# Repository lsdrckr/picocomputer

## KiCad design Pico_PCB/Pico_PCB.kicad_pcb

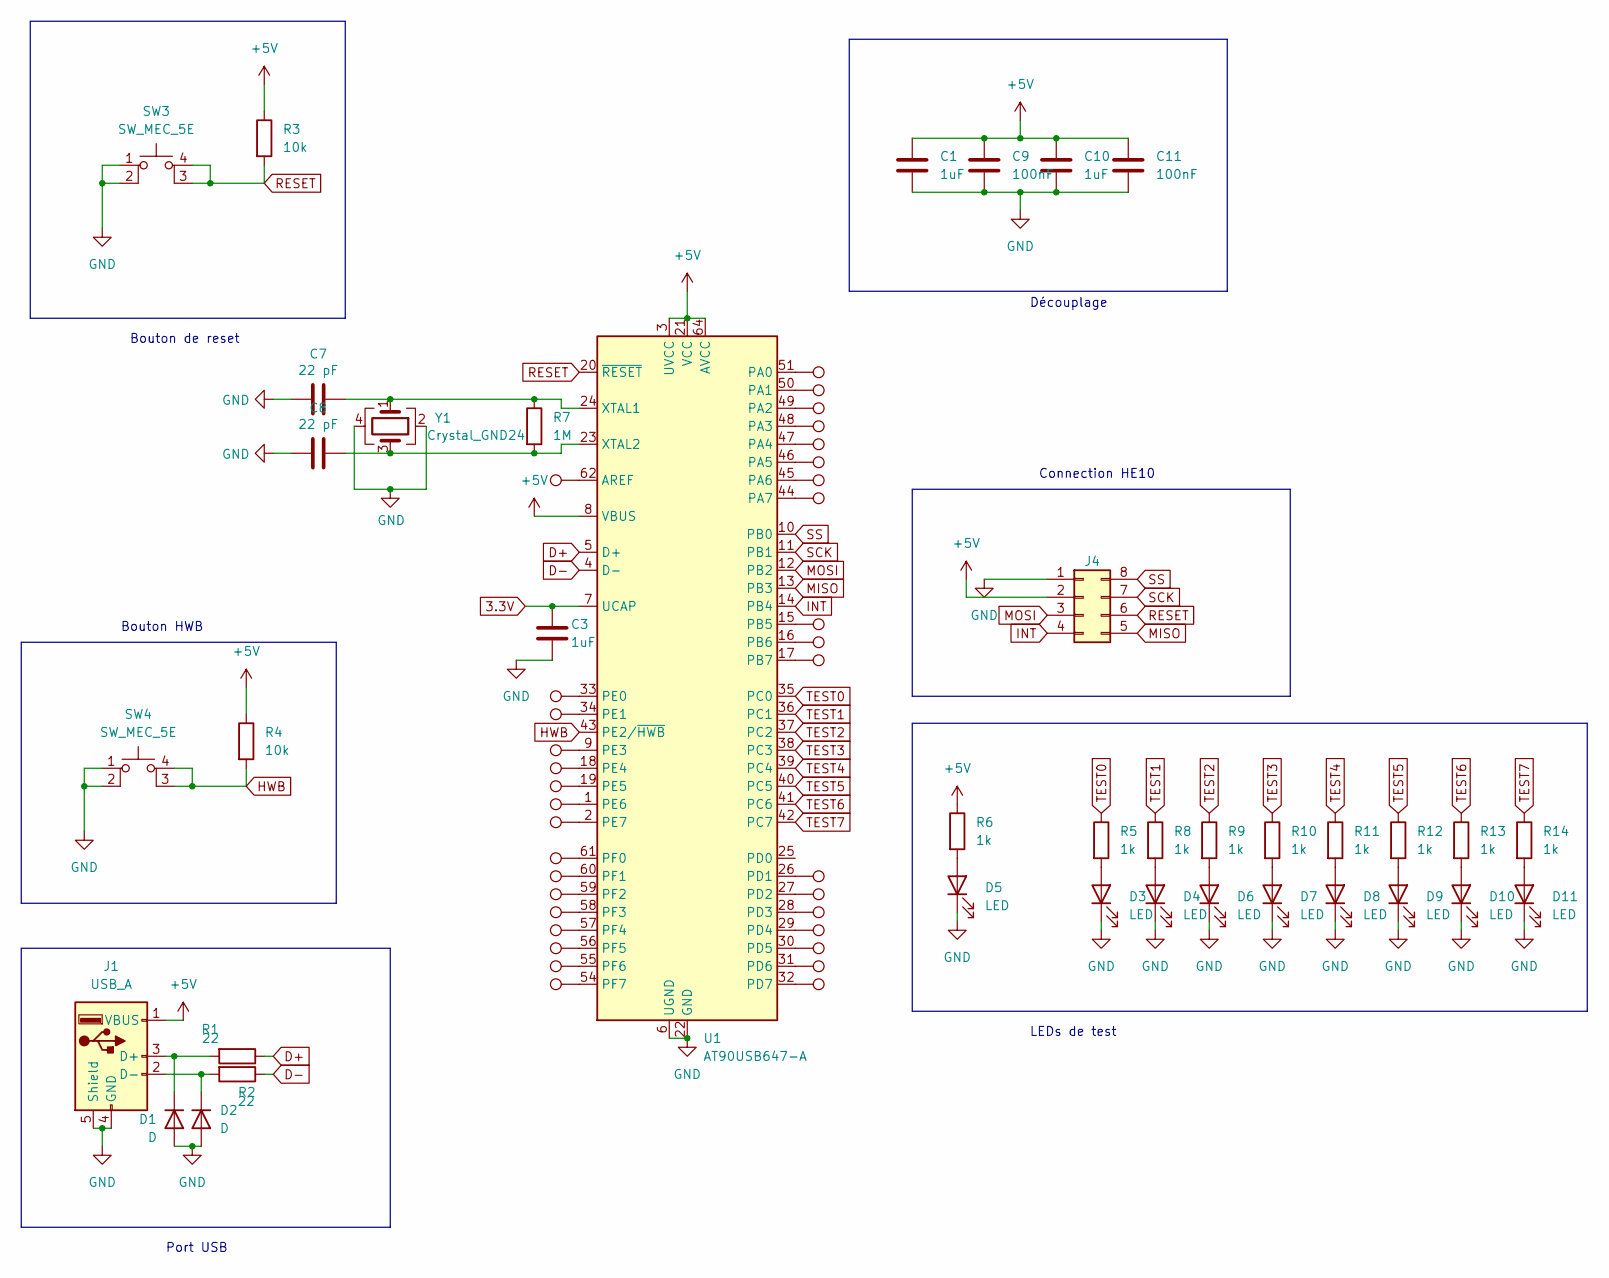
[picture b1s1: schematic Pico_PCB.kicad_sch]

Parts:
C1, C3, C10: 1uF; C_0603_1608Metric_Pad1.08x0.95mm_HandSolder
C7, C8: 22 pF; C_0603_1608Metric_Pad1.08x0.95mm_HandSolder
C9, C11: 100nF; C_0603_1608Metric_Pad1.08x0.95mm_HandSolder
D1, D2: D; D_0603_1608Metric_Pad1.05x0.95mm_HandSolder
D3, D4, D5, D6, D7, D8, D9, D10, D11: LED; LED_0603_1608Metric_Pad1.05x0.95mm_HandSolder
J1: USB_A; USB-A-S-NOSILK-FEMALE
J4: Conn_02x04_Counter_Clockwise; IDC-Header_2x04_P2.54mm_Vertical
R1, R2: 22; R_0603_1608Metric_Pad0.98x0.95mm_HandSolder
R3, R4: 10k; R_0603_1608Metric_Pad0.98x0.95mm_HandSolder
R5, R6, R8, R9, R10, R11, R12, R13, R14: 1k; R_0603_1608Metric_Pad0.98x0.95mm_HandSolder
R7: 1M; R_0603_1608Metric_Pad0.98x0.95mm_HandSolder
SW3, SW4: SW_MEC_5E; TACTILE_SWITCH_SMD_5.2MM
TP1, TP2, TP3, TP4, TP5, TP6, TP7, TP8, TP9, TP10, TP11, TP13, TP14, TP15, TP16, TP17, TP18, TP19, TP20, TP21, TP22, TP23, TP24, TP25, TP26, TP27, TP28, TP29, TP30, TP31, TP32, TP33, TP34, TP35: TestPoint; TestPoint_THTPad_D1.5mm_Drill0.7mm
U1: AT90USB647-A; TQFP-64_14x14mm_P0.8mm
Y1: Crystal_GND24; Crystal_SMD_SeikoEpson_FA238-4Pin_3.2x2.5mm_HandSoldering

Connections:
3.3V: C3.1, U1.7 (UCAP)
+5V: C1.1, C9.1, C10.1, C11.1, J1.1 (VBUS), J4.2, R3.1, R4.1, R6.1, U1.3 (UVCC), U1.8 (VBUS), U1.21 (VCC), U1.52 (VCC), U1.64 (AVCC)
D+: R2.1, U1.5 (D+)
D-: R1.1, U1.4 (D-)
GND: C1.2, C3.2, C7.2, C8.2, C9.2, C10.2, C11.2, D1.2 (A), D2.2 (A), D3.1 (K), D4.1 (K), D5.1 (K), D6.1 (K), D7.1 (K), D8.1 (K), D9.1 (K), D10.1 (K), D11.1 (K), J1.4 (GND), J1.5 (Shield), J4.1, SW3.1, SW3.2, SW4.1, SW4.2, U1.6 (UGND), U1.22 (GND), U1.53 (GND), U1.63 (GND), Y1.2, Y1.4
HWB: R4.2, SW4.3 (K), SW4.4 (A), U1.43 (PE2/~HWB)
INT: J4.4, U1.14 (PB4)
MISO: J4.5, U1.13 (PB3)
MOSI: J4.3, U1.12 (PB2)
unnamed: D1.1 (K), J1.3 (D+), R2.2
unnamed: D2.1 (K), J1.2 (D-), R1.2
unnamed: D3.2 (A), R5.2
unnamed: D4.2 (A), R8.2
unnamed: D5.2 (A), R6.2
unnamed: D6.2 (A), R9.2
unnamed: D7.2 (A), R10.2
unnamed: D8.2 (A), R11.2
unnamed: D9.2 (A), R12.2
unnamed: D10.2 (A), R13.2
unnamed: D11.2 (A), R14.2
unnamed: TP22.1, U1.62 (AREF)
unnamed: TP1.1, U1.51 (PA0)
unnamed: TP2.1, U1.50 (PA1)
unnamed: TP3.1, U1.49 (PA2)
unnamed: TP4.1, U1.48 (PA3)
unnamed: TP5.1, U1.47 (PA4)
unnamed: TP6.1, U1.46 (PA5)
unnamed: TP7.1, U1.45 (PA6)
unnamed: TP8.1, U1.44 (PA7)
unnamed: TP9.1, U1.15 (PB5)
unnamed: TP10.1, U1.16 (PB6)
unnamed: TP11.1, U1.17 (PB7)
unnamed: TP13.1, U1.26 (PD1)
unnamed: TP14.1, U1.27 (PD2)
unnamed: TP15.1, U1.28 (PD3)
unnamed: TP16.1, U1.29 (PD4)
unnamed: TP17.1, U1.30 (PD5)
unnamed: TP18.1, U1.31 (PD6)
unnamed: TP19.1, U1.32 (PD7)
unnamed: TP23.1, U1.33 (PE0)
unnamed: TP35.1, U1.34 (PE1)
unnamed: TP24.1, U1.9 (PE3)
unnamed: TP25.1, U1.18 (PE4)
unnamed: TP26.1, U1.19 (PE5)
unnamed: TP27.1, U1.1 (PE6)
unnamed: TP28.1, U1.2 (PE7)
unnamed: TP29.1, U1.61 (PF0)
unnamed: TP30.1, U1.60 (PF1)
unnamed: TP31.1, U1.59 (PF2)
unnamed: TP32.1, U1.58 (PF3)
unnamed: TP33.1, U1.57 (PF4)
unnamed: TP34.1, U1.56 (PF5)
unnamed: TP21.1, U1.55 (PF6)
unnamed: TP20.1, U1.54 (PF7)
unnamed: C7.1, R7.1, U1.24 (XTAL1), Y1.1
unnamed: C8.1, R7.2, U1.23 (XTAL2), Y1.3
RESET: J4.6, R3.2, SW3.3 (K), SW3.4 (A), U1.20 (~RESET)
SCK: J4.7, U1.11 (PB1)
SS: J4.8, U1.10 (PB0)
TEST0: R5.1, U1.35 (PC0)
TEST1: R8.1, U1.36 (PC1)
TEST2: R9.1, U1.37 (PC2)
TEST3: R10.1, U1.38 (PC3)
TEST4: R11.1, U1.39 (PC4)
TEST5: R12.1, U1.40 (PC5)
TEST6: R13.1, U1.41 (PC6)
TEST7: R14.1, U1.42 (PC7)

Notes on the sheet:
LEDs de test
Bouton de reset
Découplage
Bouton HWB
Port USB
Connection HE10

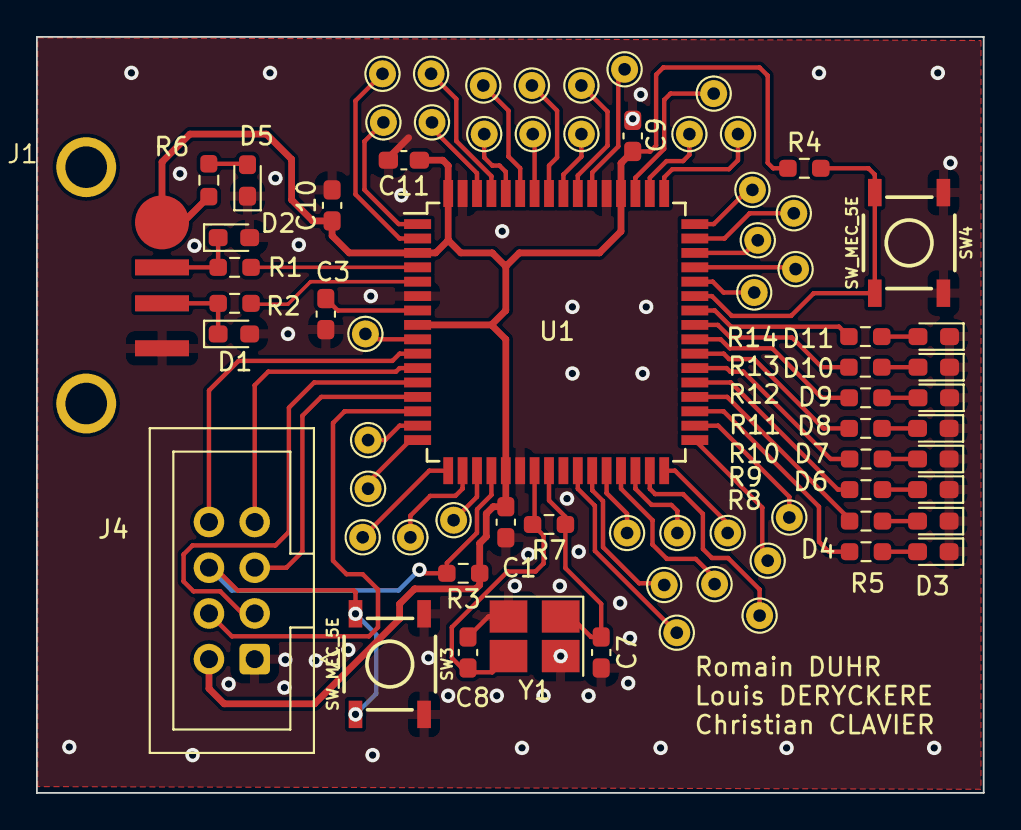
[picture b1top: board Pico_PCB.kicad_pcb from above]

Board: 2 copper layers, 52.6 x 42.0 mm, 72 parts (0 on the bottom side), 67 nets.

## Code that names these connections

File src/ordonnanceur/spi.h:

#ifndef __SPI_H__
#define __SPI_H__

#include <avr/io.h>
#include <util/delay.h>
#include <avr/interrupt.h>

#define CTC1    WGM12
#define MISO    PB4
#define MOSI    PB3
#define SCK     PB5
#define SS      PB2
#define SS2     PC0
#define SS3     PC3
#define SS4     PD1
#define SS5     PD4
#define SS6     PD7
#define RST1    PC1
#define NB_TASK 5
#define SLEEP   0
#define AWAKE   1

void initSPI();
void selectSlaveSPI(volatile uint8_t *ssPort, volatile uint8_t ss){;
void unselectSlaveSPI(volatile uint8_t *ssPort, volatile uint8_t ss);
uint8_t transferSPI(uint8_t data);
int main();

#endif

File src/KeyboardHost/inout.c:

#include "inout.h"

volatile uint8_t leds[NB_LED] = {PC7, PC6, PC5, PC4, PC3, PC2, PC1, PC0};
buffer_t buffer;
int sizeSendFlag = 0;

void initSPISlave() {
    // Configurer le port MISO comme sortie 
    DDRB |= (1<<MISO);
    // Configurer le port MOSI SCK SS comme entrée
    DDRB &= ~(1 <<MOSI);
    DDRB &= ~(1<<SCK);
    DDRB &= ~(1<<SS);

    // Actvier le mode SPI
    SPCR |= (1<<SPE);

    // Actver mode esclave SPI
    SPCR &= ~(1 << MSTR);

    // Activer l'interruption SPI
    SPCR |= (1 << SPIE);

    // Activer les interruptions globales
    sei();
}

void initIO(){
    // Initialisation des leds
    for(int i=0; i<NB_LED; i++){
        DDRC |= (1<<leds[i]);
    }

    // Initialisation du buffer 
    buffer.head = -1;
    buffer.tail = -1;
    
    // Interruption slave->master
    DDRB |= (1<<INT);
    setLowOutput(&PORTB, INT);

    // Init flag d'envoi de la taille
    sizeSendFlag = 0;

    // Init spi
    initSPISlave();
    sei();
}

uint8_t isEmpty(){
    return buffer.head == -1;
}

uint8_t isFull() {
    return (buffer.tail + 1) % MAX_DATA == buffer.head;
}

uint8_t sizeBuffer(){
    if(isEmpty()) return 0;
    if(buffer.tail < buffer.head)
        return MAX_DATA - (buffer.head - buffer.tail) + 1;
    return buffer.tail - buffer.head + 1;
}

void enqueue(char key){
    if (isFull()) {
        return;
    }
    
    buffer.tail = (buffer.tail + 1) % MAX_DATA;

    buffer.data[buffer.tail] = key;
    if (isEmpty()) {
        buffer.head = 0;
    }
}

char dequeue(){
    if (isEmpty()) {
        return 0x00;
    }
    char key = buffer.data[buffer.head];

    if (buffer.head == buffer.tail) {
        // Le buffer est maintenant vide
        buffer.head = -1;
        buffer.tail = -1;
    } else {
        buffer.head = (buffer.head + 1) % MAX_DATA;
    }
    return key;
}

void setHighOutput(volatile uint8_t *port, volatile uint8_t pin){
    *port |= (1<<pin);
}

void setLowOutput(volatile uint8_t *port, volatile uint8_t pin){
	*port &= ~(1<<pin);
}

void reverseOutput(volatile uint8_t *port, volatile uint8_t pin){
    *port ^= (1<<pin);
}

void printLeds(char c){
    for(int i=0; i<NB_LED; i++){
        if(((c >> i) & 1) == 1){
            setHighOutput(&PORTC, leds[i]);
        }else{
            setLowOutput(&PORTC, leds[i]);
        }
    }
}

void clearLeds(){
    for(int i=0; i<NB_LED; i++){
        setLowOutput(&PORTC, leds[i]);
    }
}

void keyHandler(char key){
    // Sauvegarde de la clef
    enqueue(key);
    // Envoie de l'interruption
    setHighOutput(&PORTB, INT); 
}

ISR(SPI_STC_vect) {
    uint8_t receivedData = SPDR;
    switch (receivedData){
        case 0x00:
            SPDR = 0x01;
            break;
        case 0x01:
            if(!sizeSendFlag){
                SPDR = sizeBuffer();
                sizeSendFlag = 0;
                break;
            }
            SPDR = dequeue();
            if(!sizeBuffer()){
                setLowOutput(&PORTB, INT);
                sizeSendFlag = 1;                
            }
            break;
        default:
            SPDR = dequeue();
            if(!sizeBuffer()){
                setLowOutput(&PORTB, INT);
            }
            break;
    }
}

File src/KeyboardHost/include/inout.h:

#ifndef __INOUT_H__
#define __INOUT_H__

#include <avr/io.h>
#include <util/delay.h>
#include <avr/interrupt.h>

#define NB_LED 8
#define MISO PB3
#define MOSI PB2
#define SCK PB1
#define SS PB0
#define MAX_DATA 255
#define INT PB4

typedef struct{
    int head;
    int tail;
    char data[MAX_DATA];
}buffer_t;

void initSPISlave(void);
void initIO(void);
uint8_t isEmpty(void);
uint8_t isFull(void);
uint8_t sizeBuffer(void);
char dequeue(void);
void setHighOutput(volatile uint8_t *port, volatile uint8_t pin);
void setLowOutput(volatile uint8_t *port, volatile uint8_t pin);
void reverseOutput(volatile uint8_t *port, volatile uint8_t pin);
void printLeds(char c);
void clearLeds(void);
void keyHandler(char key);
void sendData(uint8_t data);
void sendType(void);
void sendKeys(void);
void sendKey(void);
#endif

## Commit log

2023-09-12 PCB_12/09
2023-09-19 PCB_19/09
2023-09-22 Routage_22_09
2023-10-03 PCB_03/09
2023-10-10 PCB_fini
2023-10-10 Ajout ZIP
2023-10-11 Gerber generation and zip file for production
2023-10-13 Début Ordonnanceur 13/10
2023-10-13 Erreur de push réparée
2023-10-17 Ordonnanceur 17/10
2023-10-24 ordonnanceur
2023-10-24 ordonnanceurV1
2023-11-14 ordonnanceur sans sleep
2023-11-15 wait
2023-11-15 gestion des temps
2023-11-15 meilleurs temps
2023-11-15 modif
2023-11-21 Modif PCB boutons
2023-11-21 affichage des keycode
2023-11-28 Presque fini les touches !
2023-12-05 Modif clavier
2023-12-05 SPI*
2023-12-07 Fin clavier, début buffer
2023-12-07 interrupt keyboard
2023-12-11 buffer size
2023-12-11 test buffer 2
2023-12-11 Initialisation liste des périphériques
2023-12-12 conflit
2023-12-12 conflict
2023-12-12 error
2023-12-12 début spi
2023-12-12 Reconnaissance périphériques HE10
2023-12-12 keyboard
2023-12-12 transfert d'une touche
2023-12-14 grabkey
2023-12-14 Interruption
2023-12-14 interrupt
2023-12-14 gestion interrupt
2023-12-14 clavier envoie des touches mais réception bugué par moment
2023-12-14 librairie device
2023-12-15 checkinterrupt
2023-12-15 lib serial et debug lib device
2023-12-16 ascii extend
2023-12-16 test du spi
2023-12-16 tentative résolution bug temps spi
2023-12-16 on peut check les devices ainsi que vérifier les interruptions et récupérer une clé du clavier
2023-12-21 Modifications mineures
2023-12-21 Essai tableau de touches
2023-12-21 Suppression des temps d'attentes
2023-12-21 Test erreur SPI
2024-01-17 version pc fixe romain
2024-01-17 remove test
2024-01-17 remove spi
2024-01-17 last commit
2024-01-17 last last commit
2024-01-17 erreur push
2024-01-18 Envoie d'une touche à la fois fonctionne
